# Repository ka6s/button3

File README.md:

Map the Raspberry PI GPIO into I2C for the ORDROID and use Ints

The board has two I2C GPIO extender parts which map the inputs from the 
Raspberry PI to the ODROID. This is specifically for the PiHPSDR 
application.
# button3

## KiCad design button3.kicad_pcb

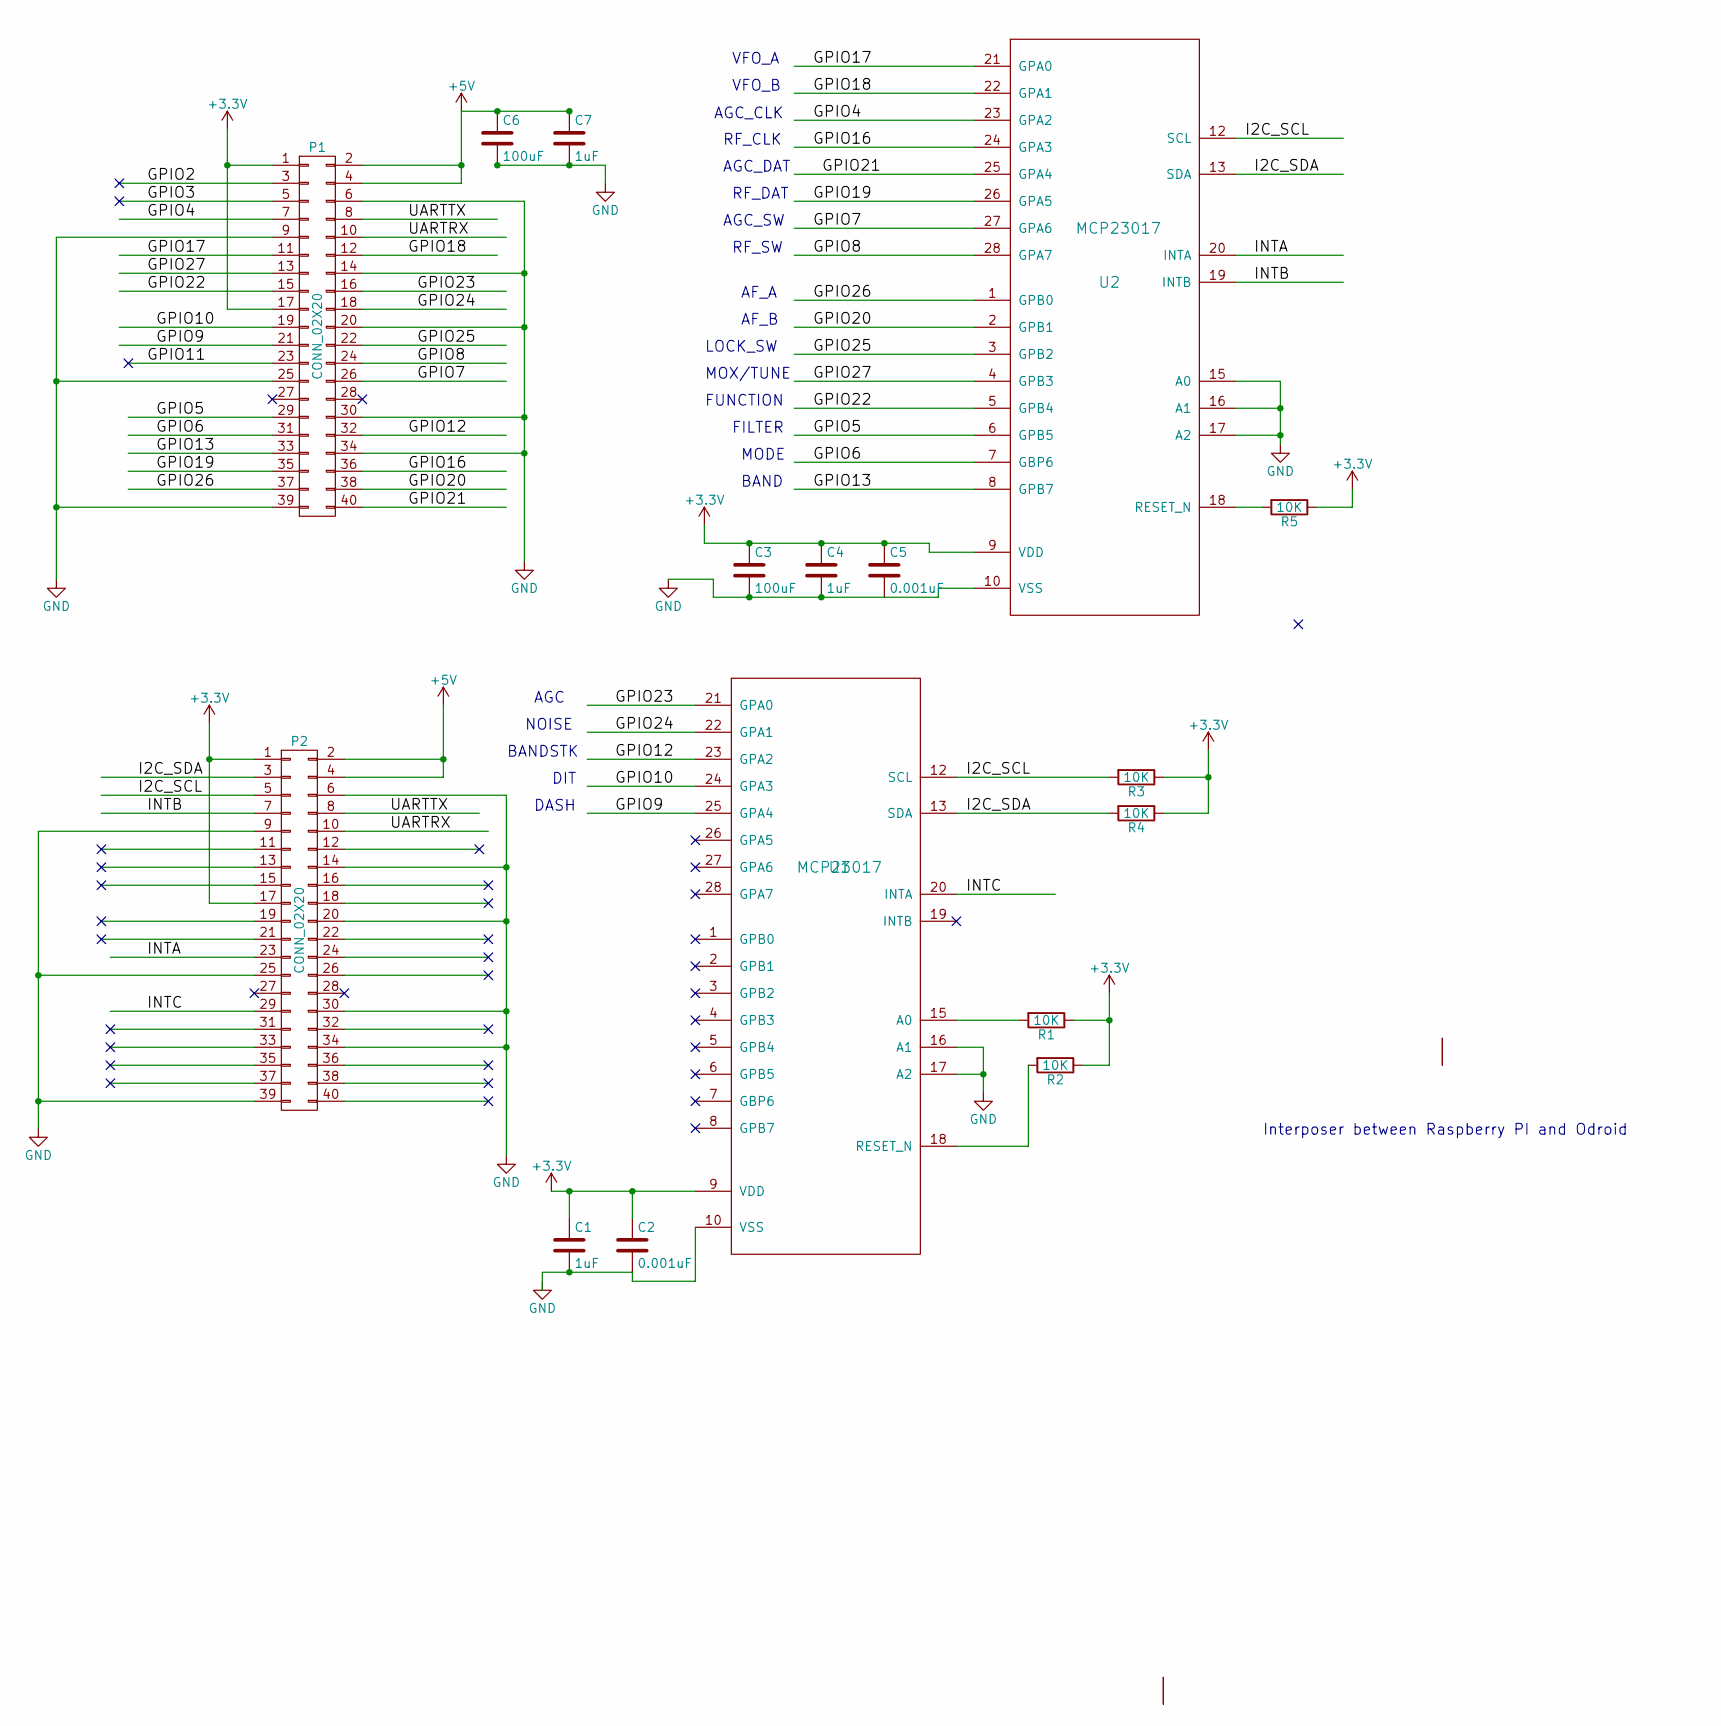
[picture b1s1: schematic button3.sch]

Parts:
C1, C4, C7: 1uF; C_1206_HandSoldering
C2, C5: 0.001uF; C_1206_HandSoldering
C3, C6: 100uF; C_1210_HandSoldering
P1, P2: CONN_02X20; Socket_Strip_Straight_2x20
R1, R2, R3, R4, R5: 10K; R_1206_HandSoldering
U1, U2: MCP23017; DIP-28_W7.62mm

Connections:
+3V3: C1.1, C2.1, C3.1, C4.1, C5.1, P1.1, P1.17, P2.1, P2.17, R1.1, R2.1, R3.1, R4.1, R5.1, U1.9 (VDD), U2.9 (VDD)
+5V: C6.1, C7.1, P1.2, P1.4, P2.2, P2.4
/GPIO2: P1.3
/GPIO3: P1.5
/GPIO4: P1.7, U2.23 (GPA2)
/GPIO5: P1.29, U2.6 (GPB5)
/GPIO6: P1.31, U2.7 (GBP6)
/GPIO7: P1.26, U2.27 (GPA6)
/GPIO8: P1.24, U2.28 (GPA7)
/GPIO9: P1.21, U1.25 (GPA4)
/GPIO10: P1.19, U1.24 (GPA3)
/GPIO11: P1.23
/GPIO12: P1.32, U1.23 (GPA2)
/GPIO13: P1.33, U2.8 (GPB7)
/GPIO16: P1.36, U2.24 (GPA3)
/GPIO17: P1.11, U2.21 (GPA0)
/GPIO18: P1.12, U2.22 (GPA1)
/GPIO19: P1.35, U2.26 (GPA5)
/GPIO20: P1.38, U2.2 (GPB1)
/GPIO21: P1.40, U2.25 (GPA4)
/GPIO22: P1.15, U2.5 (GPB4)
/GPIO23: P1.16, U1.21 (GPA0)
/GPIO24: P1.18, U1.22 (GPA1)
/GPIO25: P1.22, U2.3 (GPB2)
/GPIO26: P1.37, U2.1 (GPB0)
/GPIO27: P1.13, U2.4 (GPB3)
/I2C_SCL: P2.5, R3.2, U1.12 (SCL), U2.12 (SCL)
/I2C_SDA: P2.3, R4.2, U1.13 (SDA), U2.13 (SDA)
/INTA: P2.23, U2.20 (INTA)
/INTB: P2.7, U2.19 (INTB)
/INTC: P2.29, U1.20 (INTA)
/UARTRX: P1.10, P2.10
/UARTTX: P1.8, P2.8
unnamed: R1.2, U1.15 (A0)
unnamed: R2.2, U1.18 (RESET_N)
unnamed: R5.2, U2.18 (RESET_N)

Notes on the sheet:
Interposer between Raspberry PI and Odroid
VFO_A
VFO_B
AGC_CLK
RF_CLK
AGC_DAT
RF_DAT
AGC_SW
RF_SW
AF_A
AF_B
LOCK_SW
MOX/TUNE
FUNCTION
FILTER
MODE
BAND
AGC
NOISE
BANDSTK
DIT
DASH

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
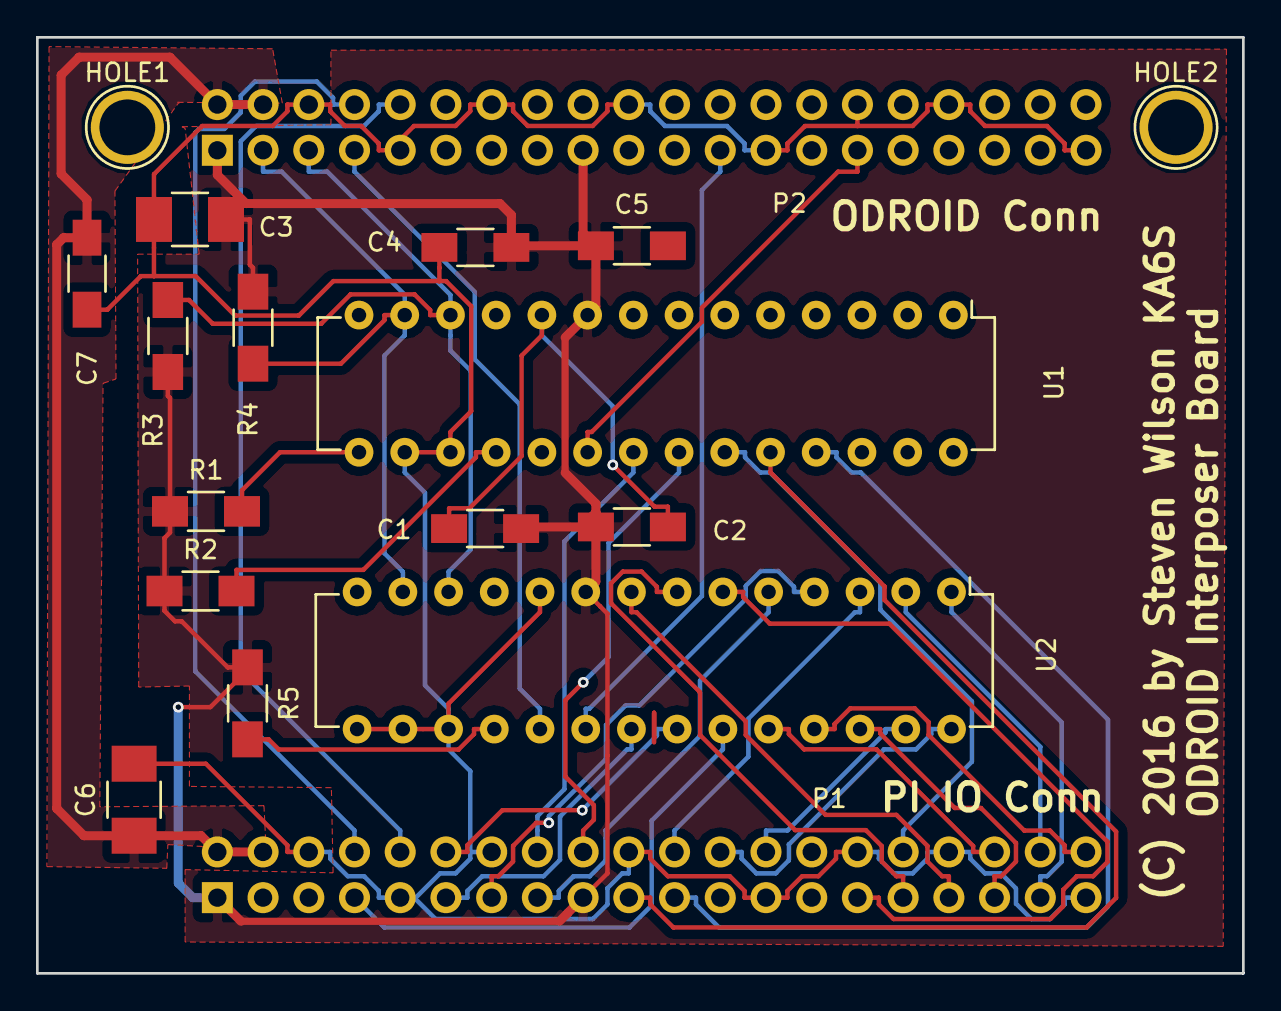
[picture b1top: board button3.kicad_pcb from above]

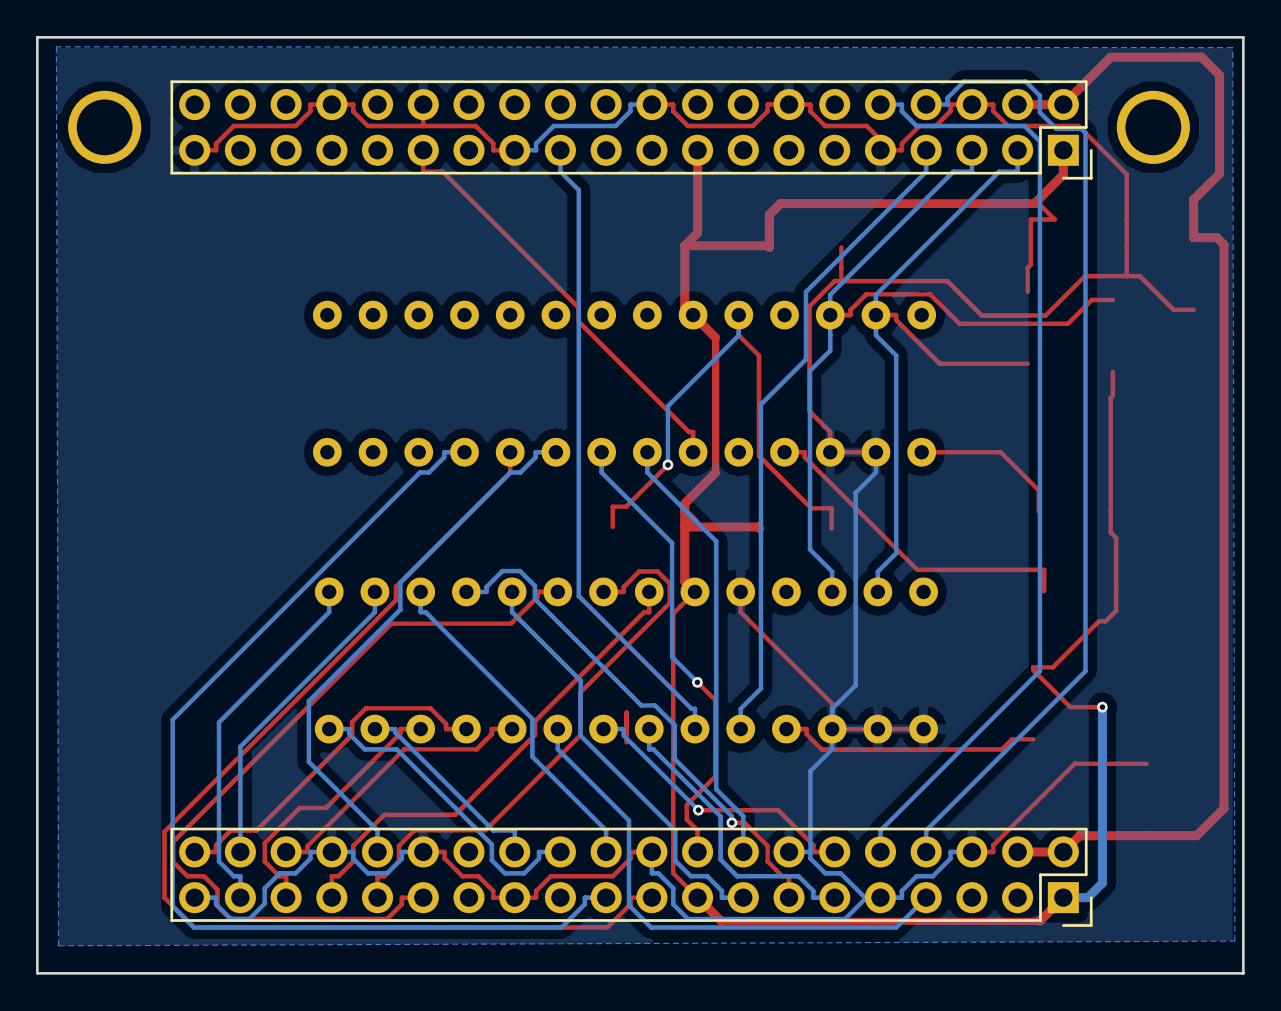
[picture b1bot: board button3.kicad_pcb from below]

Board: 2 copper layers, 67.0 x 52.0 mm, 18 parts (2 on the bottom side), 35 nets.

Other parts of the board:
HOLE1, HOLE2: 1pin

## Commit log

2016-12-20 The other stuff

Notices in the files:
button3.kicad_pcb:
(C) 2016 by Steven Wilson KA6S
